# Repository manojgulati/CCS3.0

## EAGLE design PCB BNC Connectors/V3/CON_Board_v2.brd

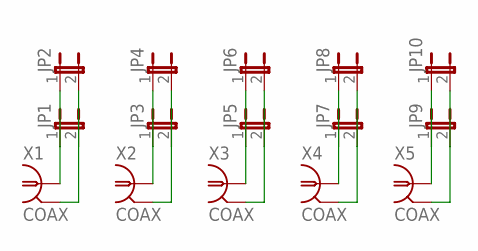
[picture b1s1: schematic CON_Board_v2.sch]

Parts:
JP1, JP2, JP3, JP4, JP5, JP6, JP7, JP8, JP9, JP10: JP1E; JP1
X1, X2, X3, X4, X5: COAX; 31-5329

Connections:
unnamed: JP1.1, JP2.1, X1.1
unnamed: JP1.2, JP2.2, X1.2, X1.3 (2), X1.4 (2), X1.5 (2)
unnamed: JP3.1, JP4.1, X2.1
unnamed: JP3.2, JP4.2, X2.2, X2.3 (2), X2.4 (2), X2.5 (2)
unnamed: JP5.1, JP6.1, X3.1
unnamed: JP5.2, JP6.2, X3.2, X3.3 (2), X3.4 (2), X3.5 (2)
unnamed: JP7.1, JP8.1, X4.1
unnamed: JP7.2, JP8.2, X4.2, X4.3 (2), X4.4 (2), X4.5 (2)
unnamed: JP9.1, JP10.1, X5.1
unnamed: JP9.2, JP10.2, X5.2, X5.3 (2), X5.4 (2), X5.5 (2)

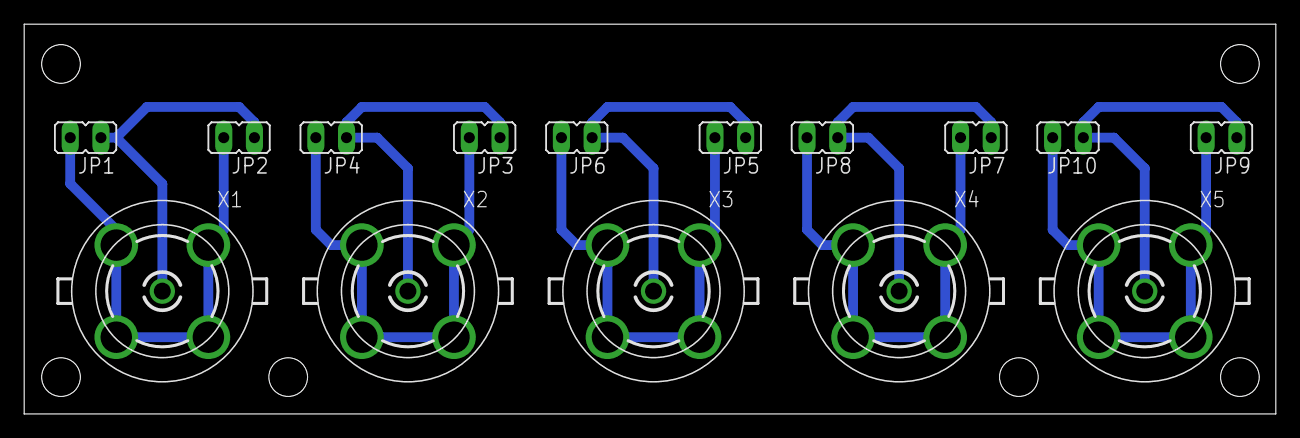
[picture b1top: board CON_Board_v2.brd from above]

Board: 2 copper layers, 103.6 x 32.2 mm, 15 parts (0 on the bottom side), 10 nets.

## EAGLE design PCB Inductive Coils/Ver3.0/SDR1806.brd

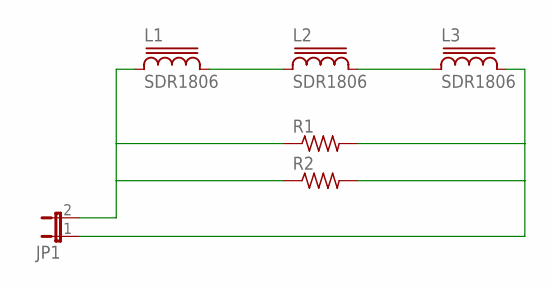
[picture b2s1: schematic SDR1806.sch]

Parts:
JP1: JP1E; JP1
L1, L2, L3: SDR1806
R1, R2: R-US_R0603; R0603

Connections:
unnamed: L1.2, L2.1
unnamed: L2.2, L3.1
unnamed: JP1.2, L1.1, R1.1, R2.1
unnamed: JP1.1, L3.2, R1.2, R2.2

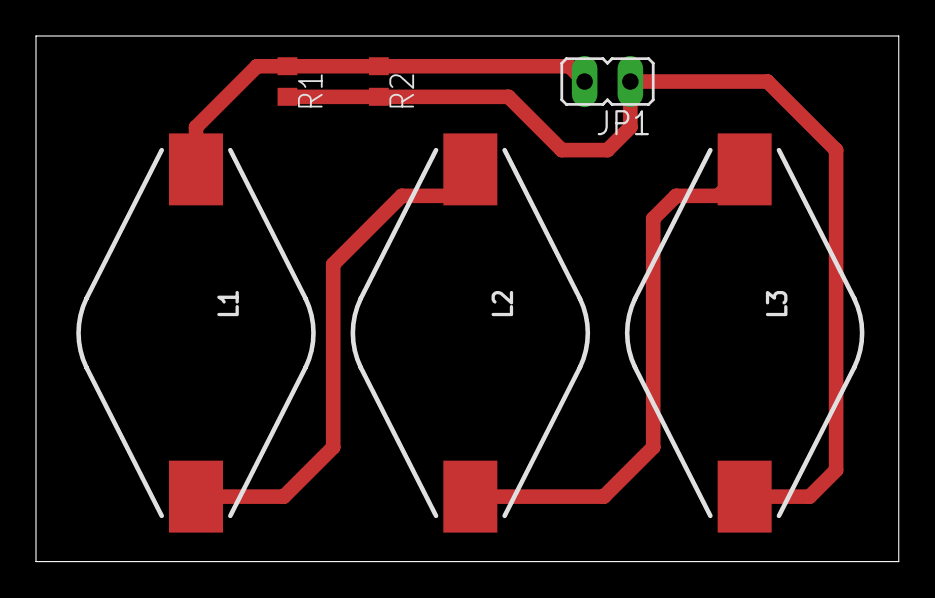
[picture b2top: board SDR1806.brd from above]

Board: 2 copper layers, 47.9 x 29.2 mm, 6 parts (0 on the bottom side), 4 nets.
